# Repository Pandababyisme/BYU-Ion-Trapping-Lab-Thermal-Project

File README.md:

# BYU-Ion-Trapping-Lab-Thermal-Project
Hi, I am Xiao Li. This is the project I worked on during summer of 2026, which is a thermal monitoring solution for an ion trapping quantum information processing lab. I will provide as detailed steps as I can here. Hopefully, it can be useful one day for you. :)

## 1. Preview
   In an ion trapping lab, different components and machines coperate as a whole to function the state-of-art quantum information process. While this happening, constronted by phsical phnominone, heat drfit will occur. And for our propuse we want to monitor the thermal information to get a better idea of what is going on.

## 2. Solution
   We proposed a solution of a system that consists one arduino, six maxchips, six pt100 sensors, and various supporting parts. In the following, we will step into more detailed description of different components, introductions of the way to make them work, assemble individual parts into a system and mislinious steps of supporting.

### 2.1)Arduino 
As the introduction, we will need one Arduino. The one we used is Arduino UNO R4 minima, personally I think it is a pretty powerful and realiable source for this project. In our solution, an arduino will role as the brain in system, which will suffit the tasks as: data collection, communicating with six maxchips via SPI protocal, transimitting data to our computer, etc. And the way we implement those tasks is through Arduino IDE. By uploading proper code to Arduino, it will perform the way as desired, and complete tasks. So we will include a Arduino IDE code file in this repository as an example of one solution. 

#### 2.11) Code design of the Arduino

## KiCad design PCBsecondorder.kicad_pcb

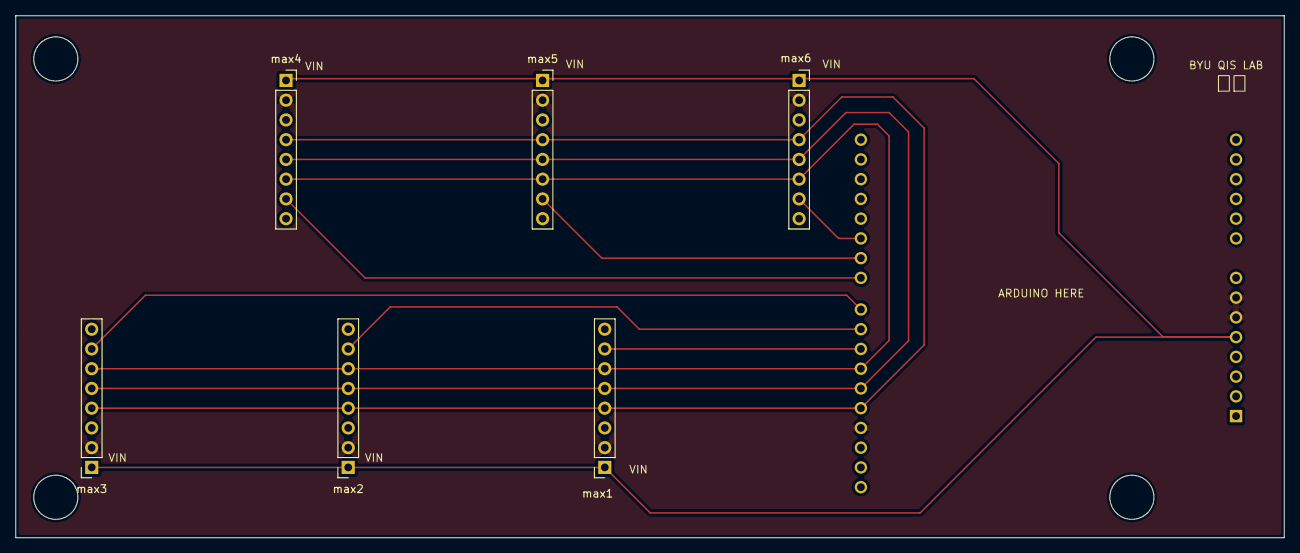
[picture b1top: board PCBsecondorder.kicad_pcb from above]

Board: 2 copper layers, 163.2 x 67.1 mm, 7 parts (1 on the bottom side), 11 nets.

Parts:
A1: Arduino_UNO_R4; Arduino_UNO_R3
max1, max2, max3, max4, max5, max6: Conn_01x08; PinSocket_1x08_P2.54mm_Vertical

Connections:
/5V: A1.5 (+5V), max1.1, max2.1, max3.1, max4.1, max5.1, max6.1
/CLK: A1.28 (D13), max1.4, max2.4, max3.4, max4.4, max5.4, max6.4
/CS1: A1.25 (D10), max1.7
/CS2: A1.24 (D9), max2.7
/CS3: A1.23 (D8), max3.7
/CS4: A1.22 (D7), max4.7
/CS5: A1.21 (D6), max5.7
/CS6: A1.20 (D5), max6.7
/GND: A1.6 (GND), A1.7 (GND), A1.29 (GND), max1.2, max2.2, max3.2, max4.2, max5.2, max6.2
/SDI: A1.26 (D11), max1.6, max2.6, max3.6, max4.6, max5.6, max6.6
/SDO: A1.27 (D12), max1.5, max2.5, max3.5, max4.5, max5.5, max6.5

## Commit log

2026-06-29 Enhance README with project and solution details
    Expanded the README with project overview, solution details, and Arduino introduction.
2026-06-29 Add files via upload
    This is our design of PCB
2026-06-29 Fix formatting and typos in README.md
    Updated headings and corrected typos in the README.
2026-06-29 3D printed case with lid
